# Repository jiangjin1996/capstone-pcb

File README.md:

# Analog Circuit Reliability for Low Earth Orbit Space Applications

In collaboration with the University of Saskatchewan, we are contributing a payload board
for the CubeSats Initiative in Canada for STEM (CUBICS). A CubeSat is a low cost, small
and approachable design for students “to engage in an end-to-end space mission
adapted to their needs and their level of comfort, expertise and readiness” (asc-csa.
gc.ca). Our payload studies the effects of space radiation on commonly used surface
mount analog Integrated Circuits (IC’s) in Low Earth Orbit (LEO). We compare different
shielding to see which provides a better effectiveness to weight ratio.

## Software

Available [here](https://github.com/kaitallaoua/capstone-cubeide)

## Setup

This project used KiCad `Version: 7.0.11-7.0.11~ubuntu22.04.1, release build` and a mix of windows builds.
Download KiCad [here](https://www.kicad.org/download/). KiCad 8 likely does work and I recommend you use it.

## Workflow

TBD (remove this once done): Someone needs to fork this repo to make further contributions to the project. Using an organization is best, I think UofS space team has one, maybe Regina team should make one? Regardless I will not be reviewing and accepting PR's to this repo.

Because using git for KiCad is like tracking binary files, I recommend to NOT rely on git handling merge conflicts. Avoid them entirely by letting only one person make changes on one branch at a time, make a PR, approve and merge and repeat and pass the baton to someone else to make changes.

## TODO

- Get I2C working (unlikely any KiCad changes)
- Get sinewave generation working 
- Add Voltage regulator
- Triple check we fit in PC104, on RADSAT-SK1 printout we dont fit in all holes, also supposed to be some notches?
- Optional: Use solder-attched external non volatile storage such as FLASH, EEPROM (or solder/glue micro sd down??)

The most substantial changes the sinwave generation. This task was assigned to Evan. Ultimately we could not get it working, thus I recommend to use a PWM wave gen from the mcu, likely add pre-amplification + current buffering, and pass it to a sharp drop off filter. The filter could be a dedicated one (probably better) or an op-amp driven one (butterworth?, wont have as good drop off without many stages).

UofRobotics is also making a PCB for their robot whose base is forked from this project, they may be a good reference for questions or idea sharing.

## Manufacturing

We used JLCPCB for `REV A` and `REV B` with great results. We also have nearly all parts ready for another revision. AT LEAST ONE MORE REVISION IS NEEDED SINCE THE FOLLOWING WERE FIXED AFTER `REV B`:

- IC1 footprint solder mask was incorrectly removed
- Micro SD card holder was facing the wrong way

Our manufacturing procedure was as follows:

Order from JLC (1 week delivery), Order from Mouser/Digikey (2-4 day delivery) -> Have all parts -> Go to ED435, use microscope, have one person assist finding parts, one pick+place, apply solder paste (min 4-5 hours)-> place in oven -> done

I recommend to use the parts list available from JLCPCB or PCBWay to assemble as much of the board for you as possible, it saves alot of time but honestly building it by hand it also not that bad. Either is fine.

JLC ordering tips:
1. Search for JLC production toolkit to generate the BOM, part placement file.
2. Generate the gerber files with time stamps in the folder name to avoid confusion (only gerber is a really bad name)
3. and do not forget to generate the drill file and put it into the gerber folder(you don't need the toolkit for this)
4. You can hand pick components on JLC if the system cannot find them automatically
5. Double check the 3d model pops up after the components are selected because sometimes the auto selected parts can be the wrong ones
6. Ask for boarding cleaning on the first page of ordering
7. Select add paste for unpopulated pad & step stencil opening for easier installation in case JLC doesn't have the components? (Not sure about this but we will see)
8. These might apply to other manufacturers as well

## Resources

[KiCad 6 STM32 PCB Design Full Tutorial - Phil's Lab #65](https://www.youtube.com/watch?v=aVUqaB0IMh4)

[PCB Design Final Touches (Tips & Checklist) - Phil's Lab #131](https://www.youtube.com/watch?v=g4m91gv-4oQ)

## Front PCB

## Back PCB

## Front Copper Layer

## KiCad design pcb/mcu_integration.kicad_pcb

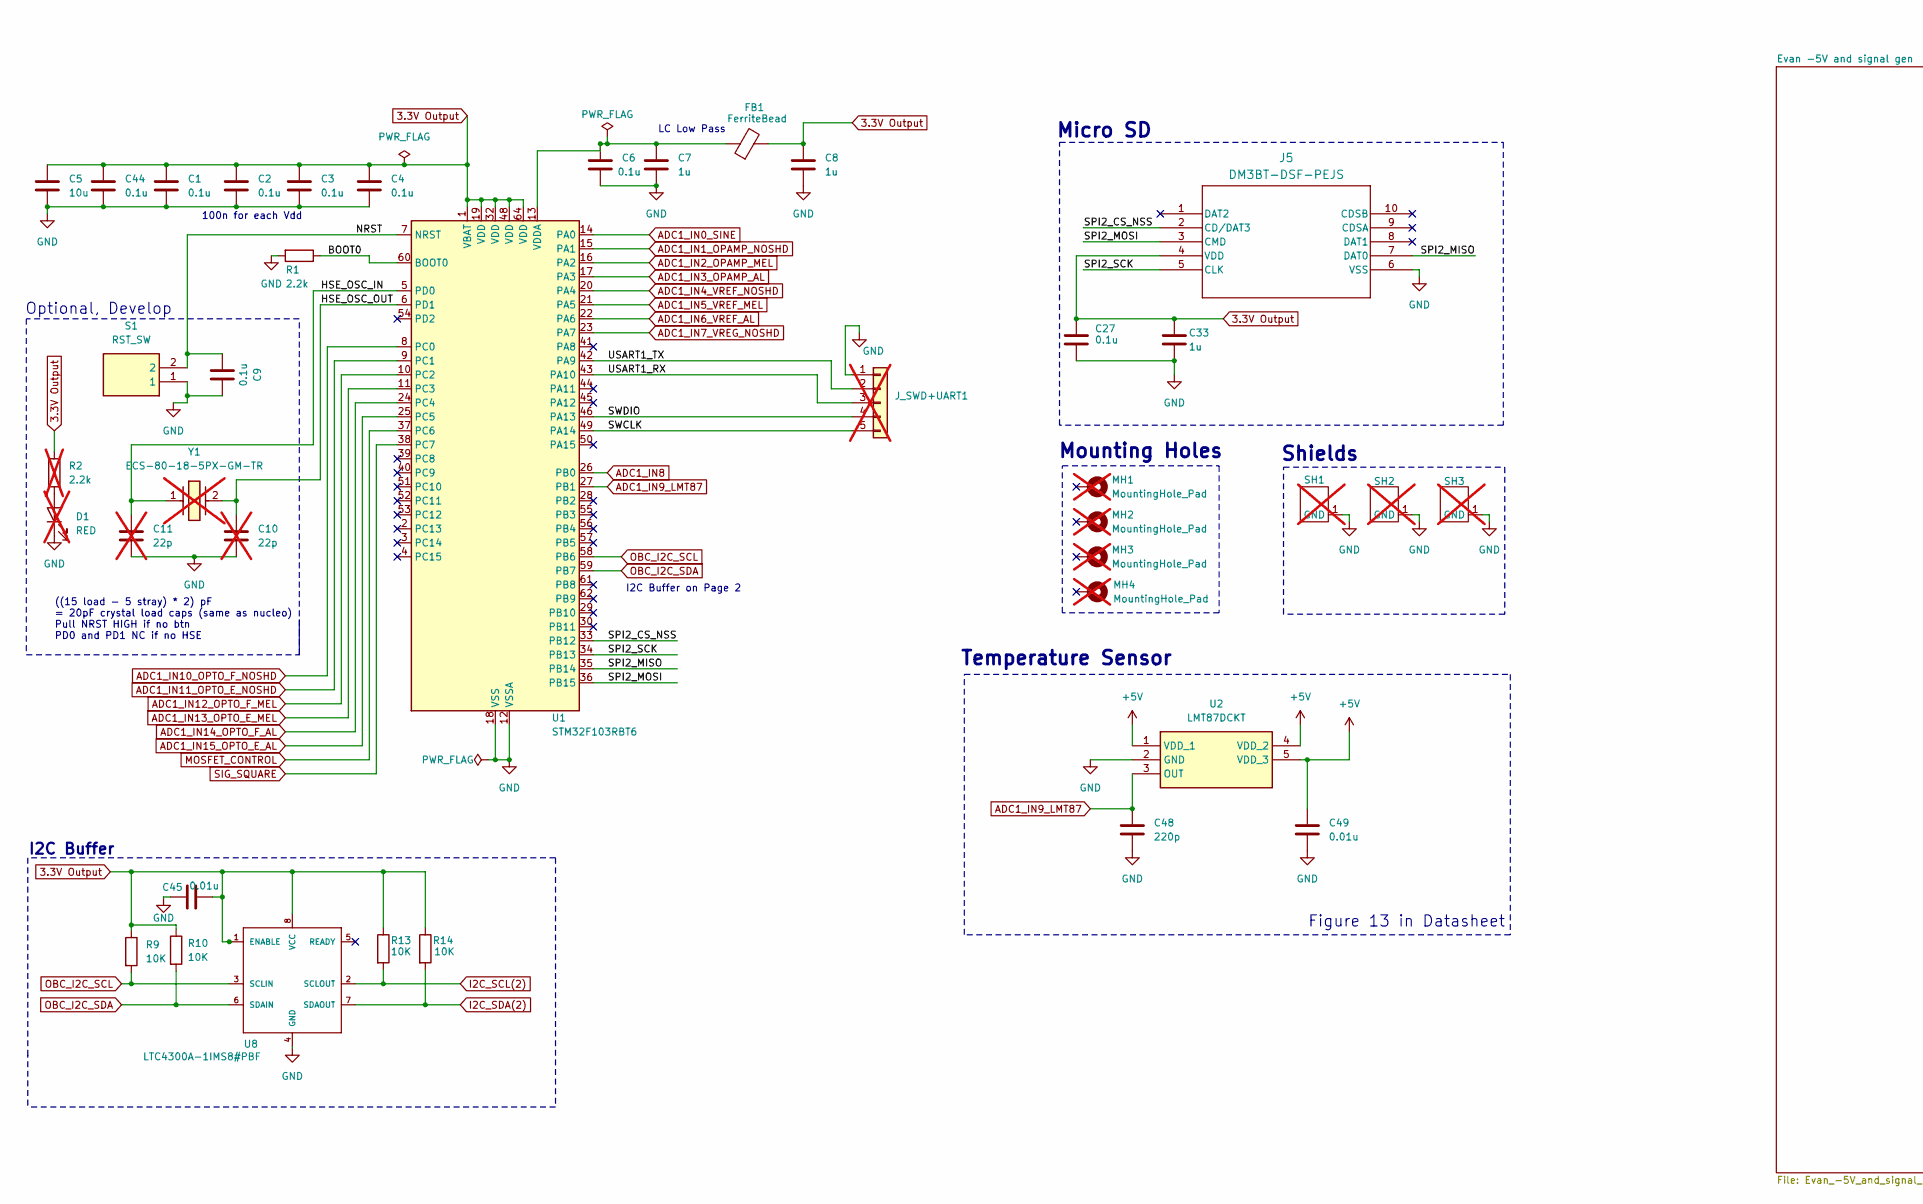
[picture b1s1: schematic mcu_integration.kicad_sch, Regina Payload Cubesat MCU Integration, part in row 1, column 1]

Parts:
C1, C2, C3, C4, C6, C9, C27, C44: 0.1u; C_0402_1005Metric; MPN C0402C104J4RALTU
C5: 10u; C_0603_1608Metric; MPN C0603C106M9PACTU
C7, C8, C33: 1u; C_0402_1005Metric; MPN 0402ZD105KAT2A
C10, C11: 22p; C_0402_1005Metric; not fitted
C45, C49: 0.01u; C_0402_1005Metric; MPN C0402C103J4RALTU
C48: 220p; C_0402_1005Metric; MPN C0402C221K8RACTU
D1: RED; LED_0603_1608Metric; not fitted
FB1: FerriteBead; L_0603_1608Metric; MPN GZ1608E601TF
J5: DM3BT-DSF-PEJS; DM3BT_DSF_PEJS; MPN DM3BT-DSF-PEJS
J_SWD+UART1: J_SWD+UART1; PinHeader_1x05_P2.54mm_Vertical; not fitted
MH1, MH2, MH3, MH4: MountingHole_Pad; MountingHole_3.18mm_6.35mm_Pad; not fitted
R1: 2.2k; R_0402_1005Metric; MPN CRCW04022K20FKTD
R2: 2.2k; R_0402_1005Metric; MPN CRCW04022K20FKTD; not fitted
R9, R10, R13, R14: 10K; R_0402_1005Metric; MPN CRCW040210K0FKTD
S1: RST_SW; 95C04A3GWRT; Mouser Part Number 706-95C04A3GWRT
SH1: AD844 Shield; not fitted
SH2: FOD814 Shield; not fitted
SH3: REF192 Shield; not fitted
U1: STM32F103RBT6; LQFP-64_10x10mm_P0.5mm; MPN STM32F103RBT6
U2: LMT87DCKT; SOT65P210X110-5N; Mouser Part Number 595-LMT87DCKT
U8: LTC4300A-1IMS8#PBF; LTC4300A-1IMS8_PBF; MPN LTC4300A-1IMS8#PBF
Y1: ECS-80-18-5PX-GM-TR; ECS80185PXGMTR; Mouser Part Number 520-80-18-5PX-GM-TR; not fitted

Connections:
3.3V Output: C1.1, C2.1, C3.1, C4.1, C5.1, C8.1, C27.1, C33.1, C44.1, C45.2, FB1.2, J5.4 (VDD), R2.1, R9.1, R10.1, R13.1, R14.1, U1.1 (VBAT), U1.19 (VDD), U1.32 (VDD), U1.48 (VDD), U1.64 (VDD), U8.1 (ENABLE), U8.8 (VCC); also elsewhere on the board
+5V: C49.1, U2.1 (VDD_1), U2.4 (VDD_2), U2.5 (VDD_3); also elsewhere on the board
/BOOT0: R1.1, U1.60 (BOOT0)
/HSE_OSC_IN: C11.1, U1.5 (PD0), Y1.1
/HSE_OSC_OUT: C10.1, U1.6 (PD1), Y1.2
/NRST: C9.2, S1.2, U1.7 (NRST)
/SPI2_CS_NSS: J5.2 (CD/DAT3), U1.33 (PB12)
/SPI2_MISO: J5.7 (DAT0), U1.35 (PB14)
/SPI2_MOSI: J5.3 (CMD), U1.36 (PB15)
/SPI2_SCK: J5.5 (CLK), U1.34 (PB13)
/SWCLK: J_SWD+UART1.5, U1.49 (PA14)
/SWDIO: J_SWD+UART1.4, U1.46 (PA13)
/USART1_RX: J_SWD+UART1.3, U1.43 (PA10)
/USART1_TX: J_SWD+UART1.2, U1.42 (PA9)
ADC1_IN0_SINE: U1.14 (PA0); also elsewhere on the board
ADC1_IN1_OPAMP_NOSHD: U1.15 (PA1); also elsewhere on the board
ADC1_IN2_OPAMP_MEL: U1.16 (PA2); also elsewhere on the board
ADC1_IN3_OPAMP_AL: U1.17 (PA3); also elsewhere on the board
ADC1_IN4_VREF_NOSHD: U1.20 (PA4); also elsewhere on the board
ADC1_IN5_VREF_MEL: U1.21 (PA5); also elsewhere on the board
ADC1_IN6_VREF_AL: U1.22 (PA6); also elsewhere on the board
ADC1_IN7_VREG_NOSHD: U1.23 (PA7)
ADC1_IN8: U1.26 (PB0)
ADC1_IN9_LMT87: C48.1, U1.27 (PB1), U2.3 (OUT); also elsewhere on the board
ADC1_IN10_OPTO_F_NOSHD: U1.8 (PC0); also elsewhere on the board
ADC1_IN11_OPTO_E_NOSHD: U1.9 (PC1); also elsewhere on the board
ADC1_IN12_OPTO_F_MEL: U1.10 (PC2); also elsewhere on the board
ADC1_IN13_OPTO_E_MEL: U1.11 (PC3); also elsewhere on the board
ADC1_IN14_OPTO_F_AL: U1.24 (PC4); also elsewhere on the board
ADC1_IN15_OPTO_E_AL: U1.25 (PC5); also elsewhere on the board
GND: C1.2, C2.2, C3.2, C4.2, C5.2, C6.2, C7.2, C8.2, C9.1, C10.2, C11.2, C27.2, C33.2, C44.2, C45.1, C48.2, C49.2, D1.1 (K), J5.6 (VSS), J_SWD+UART1.1, R1.2, S1.1, SH1.1 (GND_1), SH2.1 (GND_1), SH3.1 (GND_1), U1.12 (VSSA), U1.18 (VSS), U1.31 (VSS), U1.47 (VSS), U1.63 (VSS), U2.2 (GND), U8.4 (GND); also elsewhere on the board
I2C_SCL(2): R13.2, U8.2 (SCLOUT); also elsewhere on the board
I2C_SDA(2): R14.2, U8.7 (SDAOUT); also elsewhere on the board
MOSFET_CONTROL: U1.37 (PC6); also elsewhere on the board
unnamed: C6.1, C7.1, FB1.1, U1.13 (VDDA)
OBC_I2C_SCL: R9.2, U1.58 (PB6), U8.3 (SCLIN)
OBC_I2C_SDA: R10.2, U1.59 (PB7), U8.6 (SDAIN)
SIG_SQUARE: U1.38 (PC7); also elsewhere on the board

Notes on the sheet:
((15 load - 5 stray) * 2) pF = 20pF crystal load caps (same as nucleo) Pull NRST HIGH if no btn PD0 and PD1 NC if no HSE
Mounting Holes
Micro SD
Optional, Develop
Shields
I2C Buffer on Page 2
Temperature Sensor
100n for each Vdd
Figure 13 in Datasheet
LC Low Pass
I2C Buffer

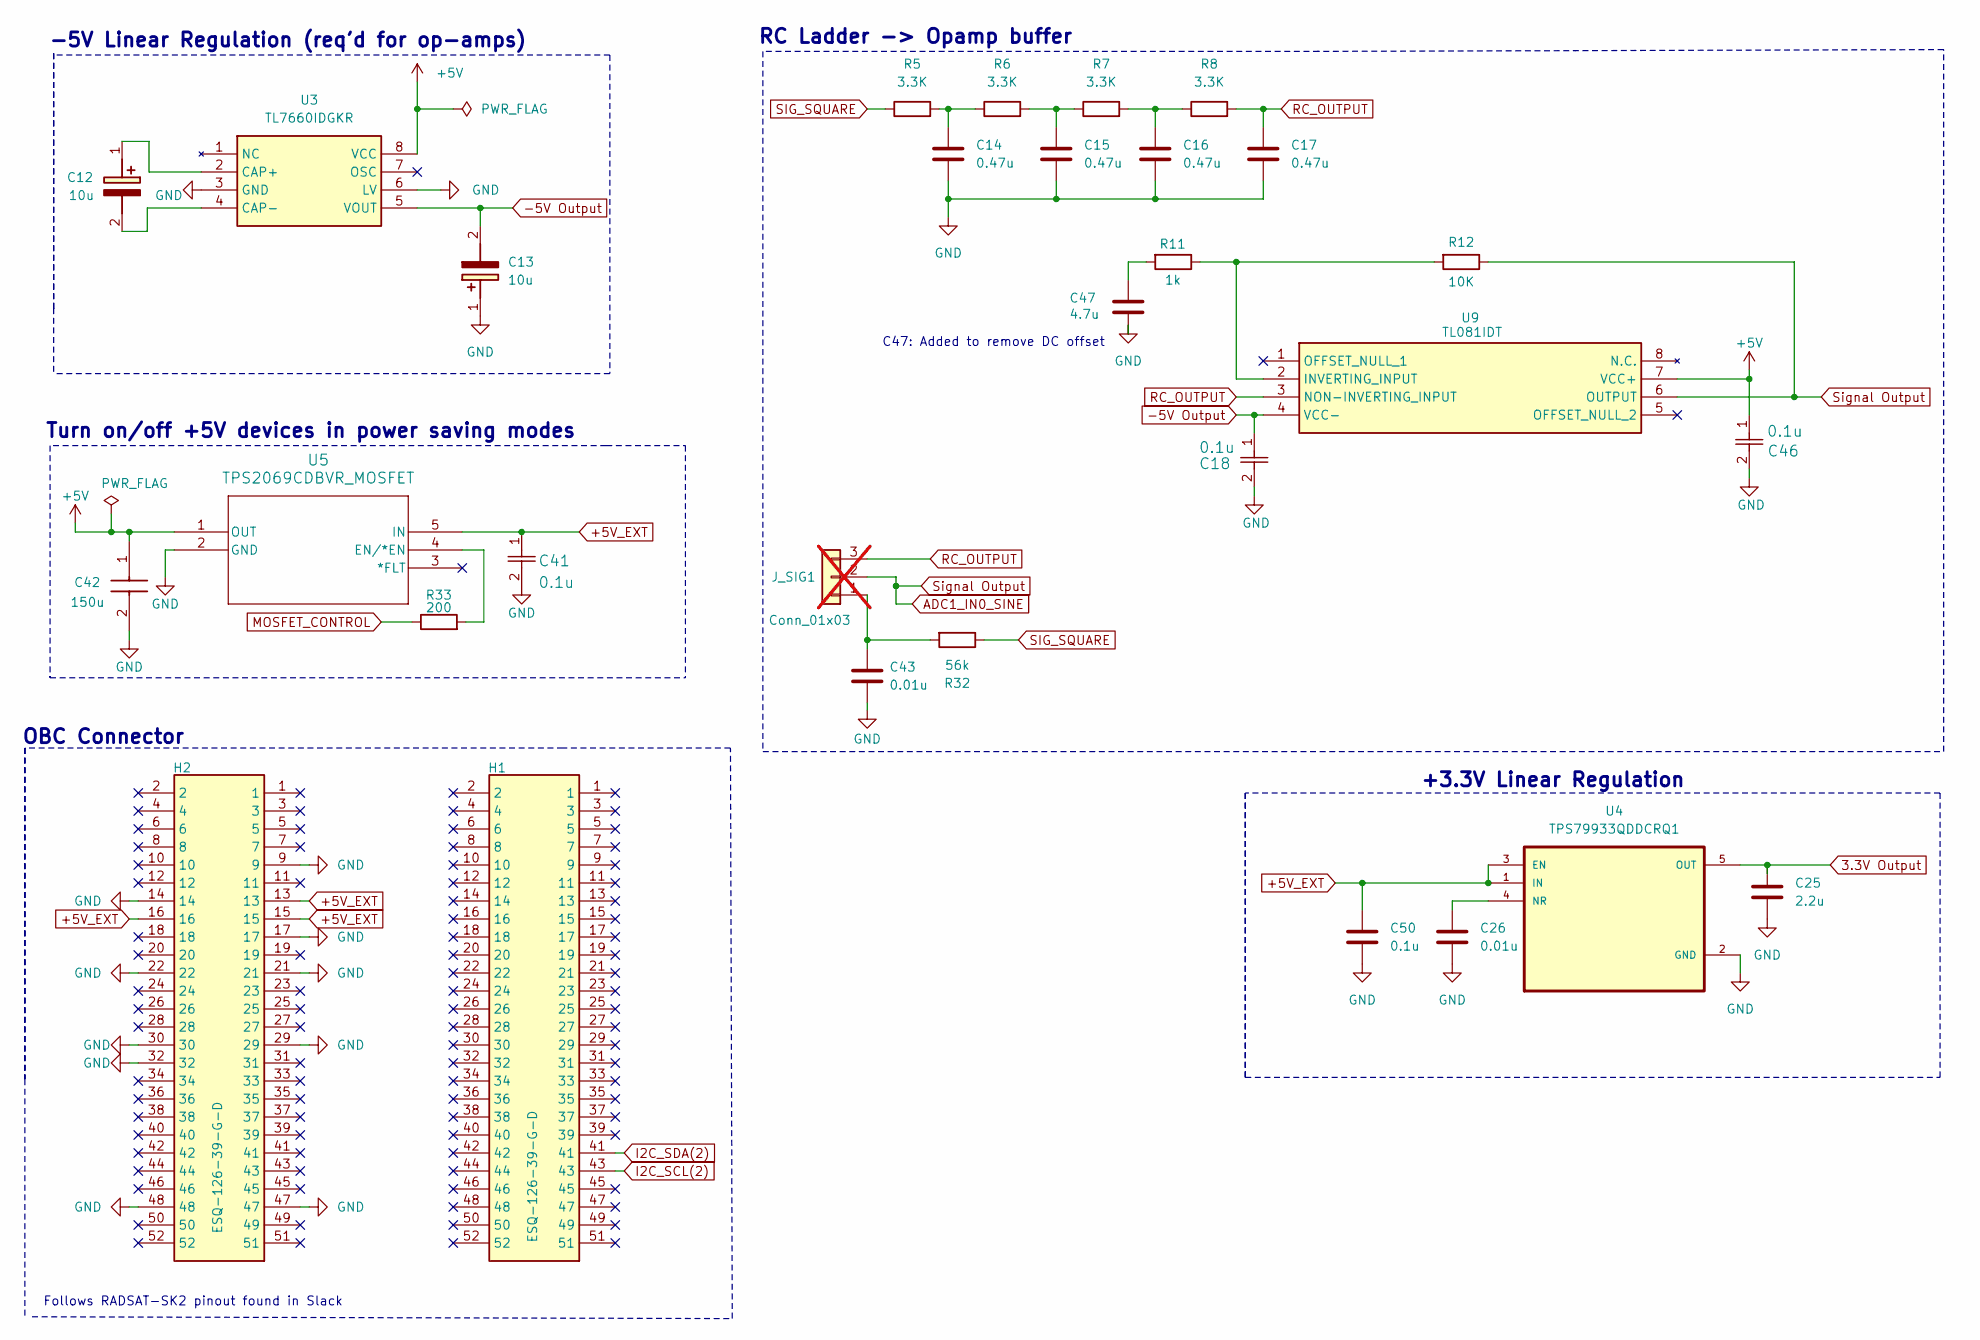
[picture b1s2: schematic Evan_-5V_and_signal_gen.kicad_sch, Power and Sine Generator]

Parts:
C12, C13: 10u; C_0805_2012Metric; Mouser Part Number 80-T495D106K035
C14, C15, C16, C17: 0.47u; C_0402_1005Metric; MPN KGM05AR51A474KH
C18, C41, C46: 0.1u; C_0805_2012Metric; MPN C0805C104J4RALTU
C25: 2.2u; C_0603_1608Metric; MPN C0603C225K8RACTU
C26, C43: 0.01u; C_0402_1005Metric; MPN C0402C103J4RALTU
C42: 150u; CAPC3225X280N_150U; Mouser Part Number 187-CL32A157MQVNNNE
C47: 4.7u; C_0805_2012Metric; MPN C0805C475J4RACTU
C50: 0.1u; C_0402_1005Metric; MPN C0402C104J4RALTU
H1, H2: ESQ-126-39-G-D; RHDR52W64P254_2X26_6654X495X1135P; Mouser Part Number 200-ESQ12639LD
J_SIG1: Conn_01x03; PinHeader_1x03_P2.54mm_Vertical; not fitted
R5, R6, R7, R8: 3.3K; R_0402_1005Metric; MPN CRCW04023K30FKTD
R11: 1k; R_0402_1005Metric; MPN CRCW04021K00FKTD
R12: 10K; R_0402_1005Metric; MPN CRCW040210K0FKTD
R32: 56k; R_0402_1005Metric; MPN CRCW040256K0FKTD
R33: 200; R_0402_1005Metric; MPN CRCW0402200RFKTD
U3: TL7660IDGKR; SOP65P490X110-8N-actual; Mouser Part Number 595-TL7660IDGKR
U4: TPS79933QDDCRQ1; SOT95P280X110-5N; MPN TPS79933QDDCRQ1
U5: TPS2069CDBVR_MOSFET; DBV5_TEX_MF; MPN TPS2069CDBVR
U9: TL081IDT; SOIC127P600X175-8N; Mouser Part Number 511-TL081IDT

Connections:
3.3V Output: C25.1, U4.5 (OUT); also elsewhere on the board
+5V: C42.1, C46.1, U3.8 (VCC), U5.1 (OUT), U9.7 (VCC+); also elsewhere on the board
+5V_EXT: C41.1, C50.1, H2.13, H2.15, H2.16, U4.1 (IN), U4.3 (EN), U5.5 (IN)
-5V Output: C13.2 (-), C18.1, U3.5 (VOUT), U9.4 (VCC-); also elsewhere on the board
ADC1_IN0_SINE: J_SIG1.2, R12.1, U9.6 (OUTPUT); also elsewhere on the board
GND: C13.1 (+), C14.2, C15.2, C16.2, C17.2, C18.2, C25.2, C26.2, C41.2, C42.2, C43.1, C46.2, C47.2, C50.2, H2.9, H2.14, H2.17, H2.21, H2.22, H2.29, H2.30, H2.32, H2.47, H2.48, U3.3 (GND), U3.6 (LV), U4.2 (GND), U5.2 (GND); also elsewhere on the board
I2C_SCL(2): H1.43; also elsewhere on the board
I2C_SDA(2): H1.41; also elsewhere on the board
MOSFET_CONTROL: R33.1; also elsewhere on the board
unnamed: C12.1 (+), U3.2 (CAP+)
unnamed: C12.2 (-), U3.4 (CAP-)
unnamed: C14.1, R5.2, R6.1
unnamed: C15.1, R6.2, R7.1
unnamed: C16.1, R7.2, R8.1
unnamed: C47.1, R11.2
unnamed: C43.2, J_SIG1.1, R32.2
unnamed: C26.1, U4.4 (NR)
unnamed: R33.2, U5.4 (EN/*EN)
unnamed: R11.1, R12.2, U9.2 (INVERTING_INPUT)
RC_OUTPUT: C17.1, J_SIG1.3, R8.2, U9.3 (NON-INVERTING_INPUT)
SIG_SQUARE: R5.1, R32.1; also elsewhere on the board

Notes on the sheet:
OBC Connector
+3.3V Linear Regulation
-5V Linear Regulation (req'd for op-amps)
RC Ladder -> Opamp buffer
Turn on/off +5V devices in power saving modes
Follows RADSAT-SK2 pinout found in Slack
C47: Added to remove DC offset

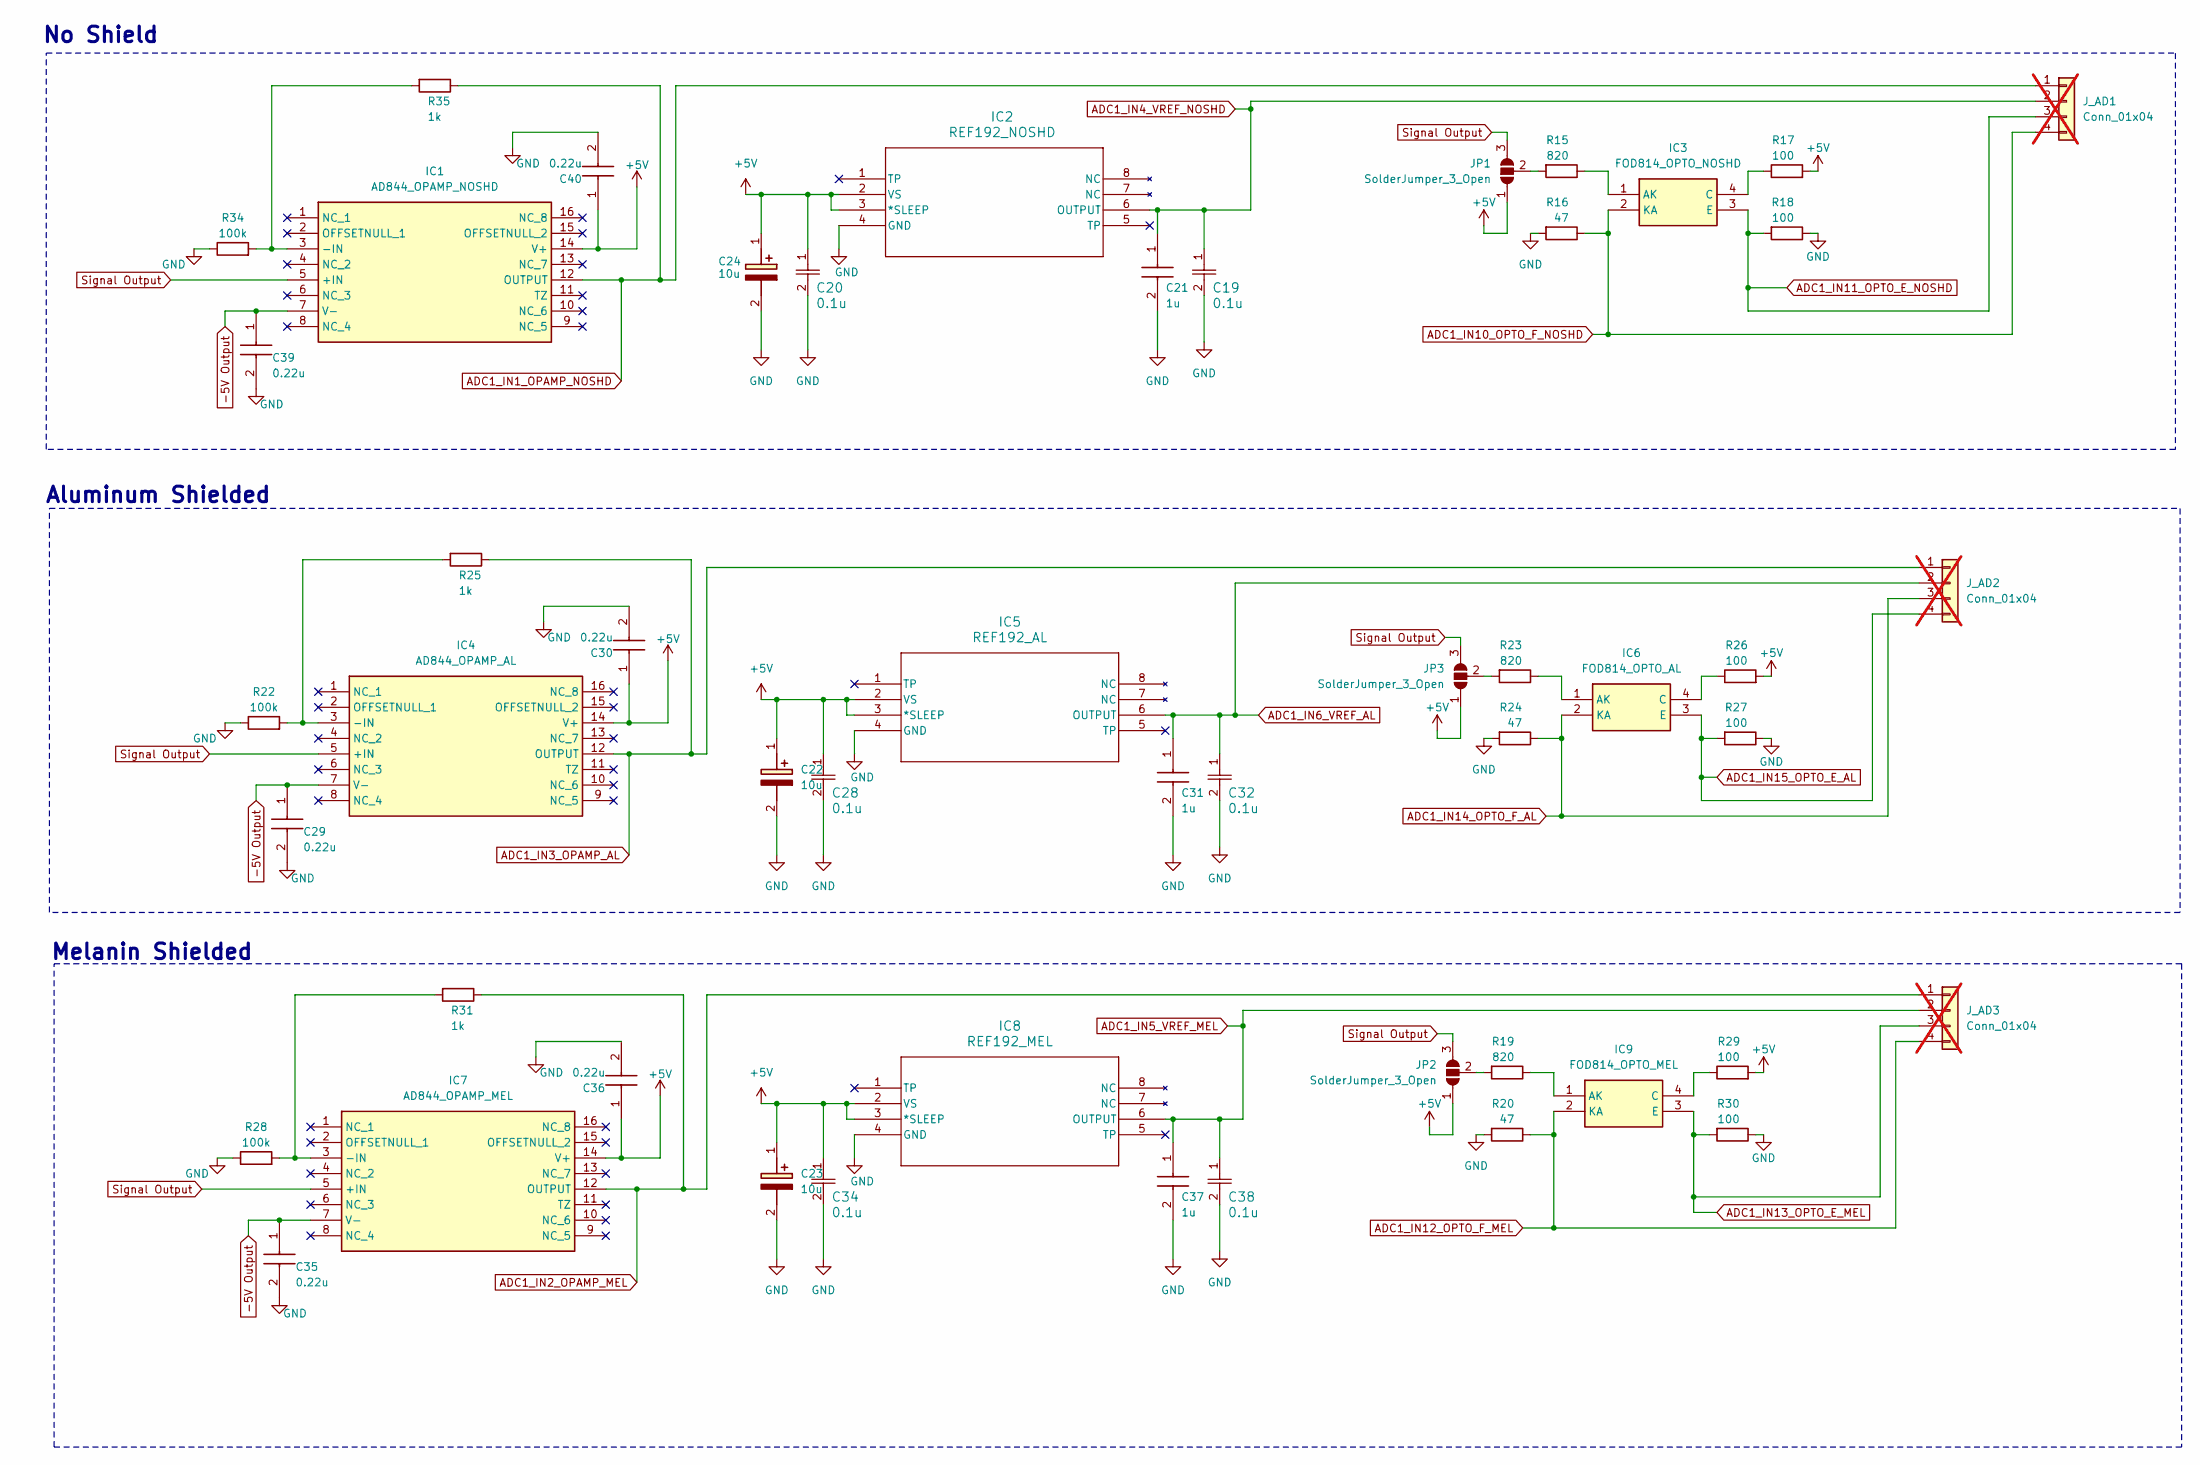
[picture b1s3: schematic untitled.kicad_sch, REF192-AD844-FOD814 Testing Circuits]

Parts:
C19, C20, C28, C32, C34, C38: 0.1u; C_0805_2012Metric; MPN C0805C104J4RALTU
C21, C31, C37: 1u; C0805-1u; Mouser Part Number 80-C0805C105Z5VACTU
C22, C23, C24: 10u; C_0805_2012Metric; Mouser Part Number 80-T495D106K035
C29, C30, C35, C36, C39, C40: 0.22u; C0805-0.22u; MPN C0805C224J4RALTU
IC1: AD844_OPAMP_NOSHD; SOIC127P1032X265-16N-AD844; Mouser Part Number 584-AD844JRZ-16-R7
IC2: REF192_NOSHD; R_8_ADI-REF; MPN REF192GSZ
IC3: FOD814_OPTO_NOSHD; SOP254P1016X385-4N-FOD; Mouser Part Number 512-FOD814SD
IC4: AD844_OPAMP_AL; SOIC127P1032X265-16N-AD844; Mouser Part Number 584-AD844JRZ-16-R7
IC5: REF192_AL; R_8_ADI-REF; MPN REF192GSZ
IC6: FOD814_OPTO_AL; SOP254P1016X385-4N-FOD; Mouser Part Number 512-FOD814SD
IC7: AD844_OPAMP_MEL; SOIC127P1032X265-16N-AD844; Mouser Part Number 584-AD844JRZ-16-R7
IC8: REF192_MEL; R_8_ADI-REF; MPN REF192GSZ
IC9: FOD814_OPTO_MEL; SOP254P1016X385-4N-FOD; Mouser Part Number 512-FOD814SD
JP1, JP2, JP3: SolderJumper_3_Open; SolderJumper-3_P2.0mm_Open_TrianglePad1.0x1.5mm
J_AD1, J_AD2, J_AD3: Conn_01x04; PinHeader_1x04_P2.54mm_Vertical; not fitted
R15, R19, R23: 820; R_0402_1005Metric; MPN CRCW0402820RFKED
R16, R20, R24: 47; R_0402_1005Metric; MPN CRCW040247R0FKTD
R17, R18, R26, R27, R29, R30: 100; R_0402_1005Metric; MPN CRCW0402100RFKTD
R22, R28, R34: 100k; R_0402_1005Metric; MPN CRCW0402100KFKTD
R25, R31, R35: 1k; R_0402_1005Metric; MPN CRCW04021K00FKTD

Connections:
+5V: C20.1, C22.1 (+), C23.1 (+), C24.1 (+), C28.1, C30.1, C34.1, C36.1, C40.1, IC1.14 (V+), IC2.2 (VS), IC2.3 (*SLEEP), IC4.14 (V+), IC5.2 (VS), IC5.3 (*SLEEP), IC7.14 (V+), IC8.2 (VS), IC8.3 (*SLEEP), JP1.1 (A), JP2.1 (A), JP3.1 (A), R17.2, R26.2, R29.2; also elsewhere on the board
-5V Output: C29.1, C35.1, C39.1, IC1.7 (V-), IC4.7 (V-), IC7.7 (V-); also elsewhere on the board
ADC1_IN0_SINE: IC1.5 (+IN), IC4.5 (+IN), IC7.5 (+IN), JP1.3 (B), JP2.3 (B), JP3.3 (B); also elsewhere on the board
ADC1_IN1_OPAMP_NOSHD: IC1.12 (OUTPUT), J_AD1.1, R35.1; also elsewhere on the board
ADC1_IN2_OPAMP_MEL: IC7.12 (OUTPUT), J_AD3.1, R31.1; also elsewhere on the board
ADC1_IN3_OPAMP_AL: IC4.12 (OUTPUT), J_AD2.1, R25.1; also elsewhere on the board
ADC1_IN4_VREF_NOSHD: C19.1, C21.1, IC2.6 (OUTPUT), J_AD1.2; also elsewhere on the board
ADC1_IN5_VREF_MEL: C37.1, C38.1, IC8.6 (OUTPUT), J_AD3.2; also elsewhere on the board
ADC1_IN6_VREF_AL: C31.1, C32.1, IC5.6 (OUTPUT), J_AD2.2; also elsewhere on the board
ADC1_IN10_OPTO_F_NOSHD: IC3.2 (KA), J_AD1.4, R16.1; also elsewhere on the board
ADC1_IN11_OPTO_E_NOSHD: IC3.3 (E), J_AD1.3, R18.2; also elsewhere on the board
ADC1_IN12_OPTO_F_MEL: IC9.2 (KA), J_AD3.4, R20.1; also elsewhere on the board
ADC1_IN13_OPTO_E_MEL: IC9.3 (E), J_AD3.3, R30.2; also elsewhere on the board
ADC1_IN14_OPTO_F_AL: IC6.2 (KA), J_AD2.3, R24.1; also elsewhere on the board
ADC1_IN15_OPTO_E_AL: IC6.3 (E), J_AD2.4, R27.2; also elsewhere on the board
GND: C19.2, C20.2, C21.2, C22.2 (-), C23.2 (-), C24.2 (-), C28.2, C29.2, C30.2, C31.2, C32.2, C34.2, C35.2, C36.2, C37.2, C38.2, C39.2, C40.2, IC2.4 (GND), IC5.4 (GND), IC8.4 (GND), R16.2, R18.1, R20.2, R22.1, R24.2, R27.1, R28.1, R30.1, R34.1; also elsewhere on the board
unnamed: IC1.3 (-IN), R34.2, R35.2
unnamed: IC3.1 (AK), R15.1
unnamed: IC3.4 (C), R17.1
unnamed: IC4.3 (-IN), R22.2, R25.2
unnamed: IC6.1 (AK), R23.1
unnamed: IC6.4 (C), R26.1
unnamed: IC7.3 (-IN), R28.2, R31.2
unnamed: IC9.1 (AK), R19.1
unnamed: IC9.4 (C), R29.1
unnamed: JP1.2 (C), R15.2
unnamed: JP2.2 (C), R19.2
unnamed: JP3.2 (C), R23.2

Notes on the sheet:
Aluminum Shielded
Melanin Shielded
No Shield

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
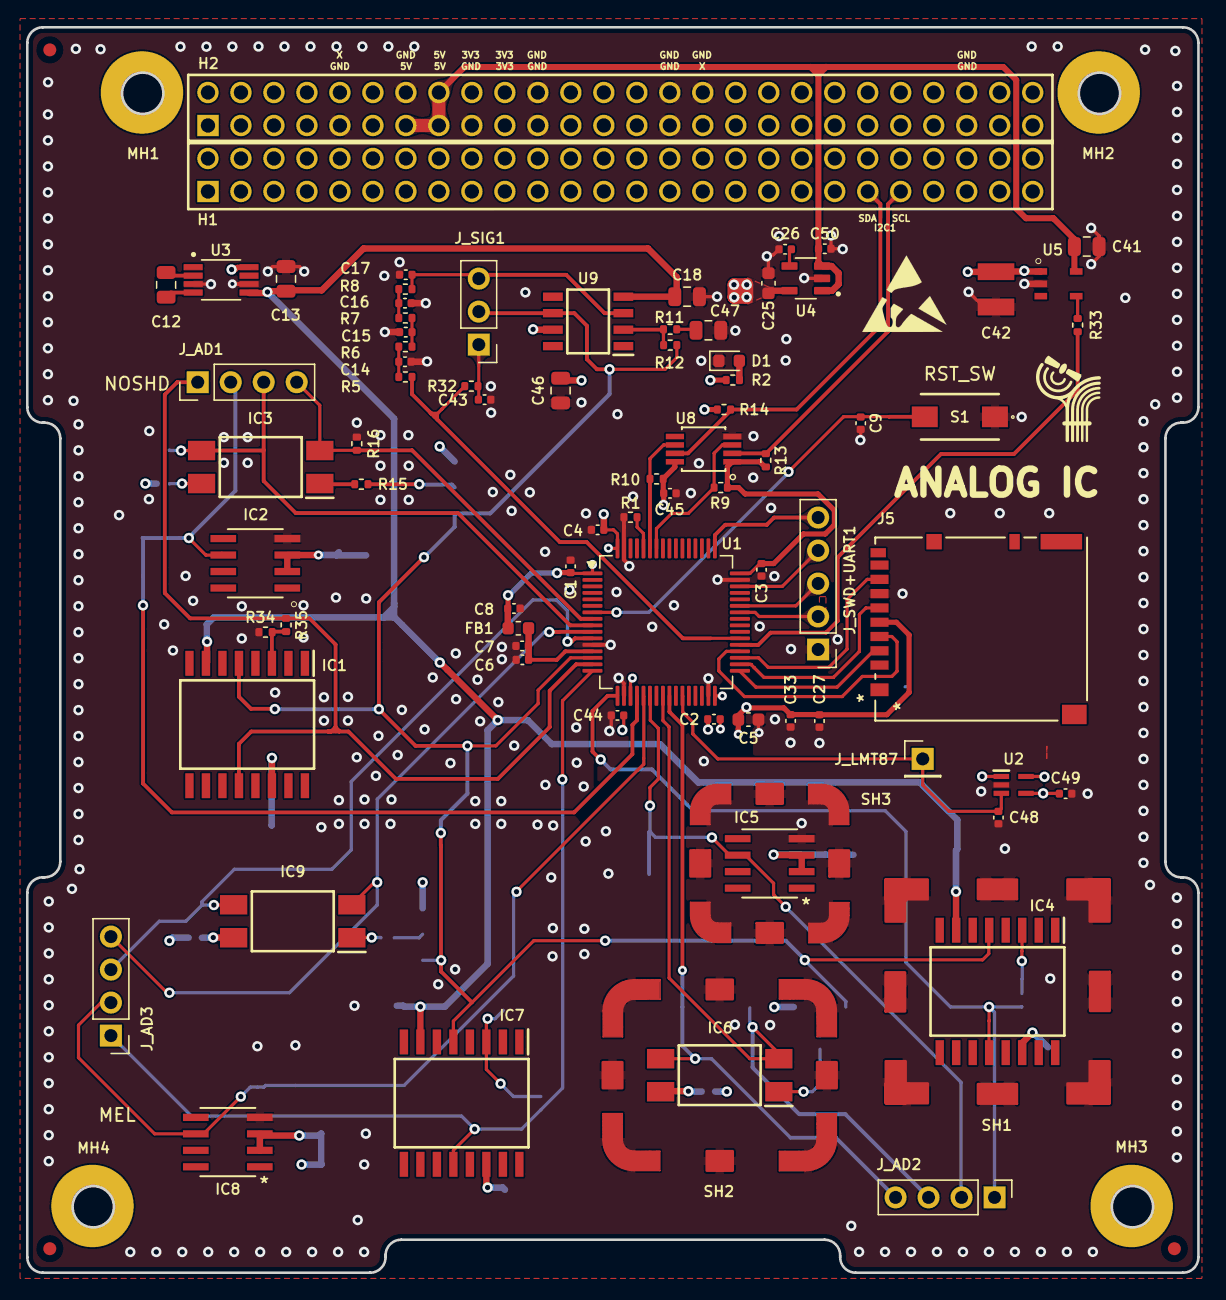
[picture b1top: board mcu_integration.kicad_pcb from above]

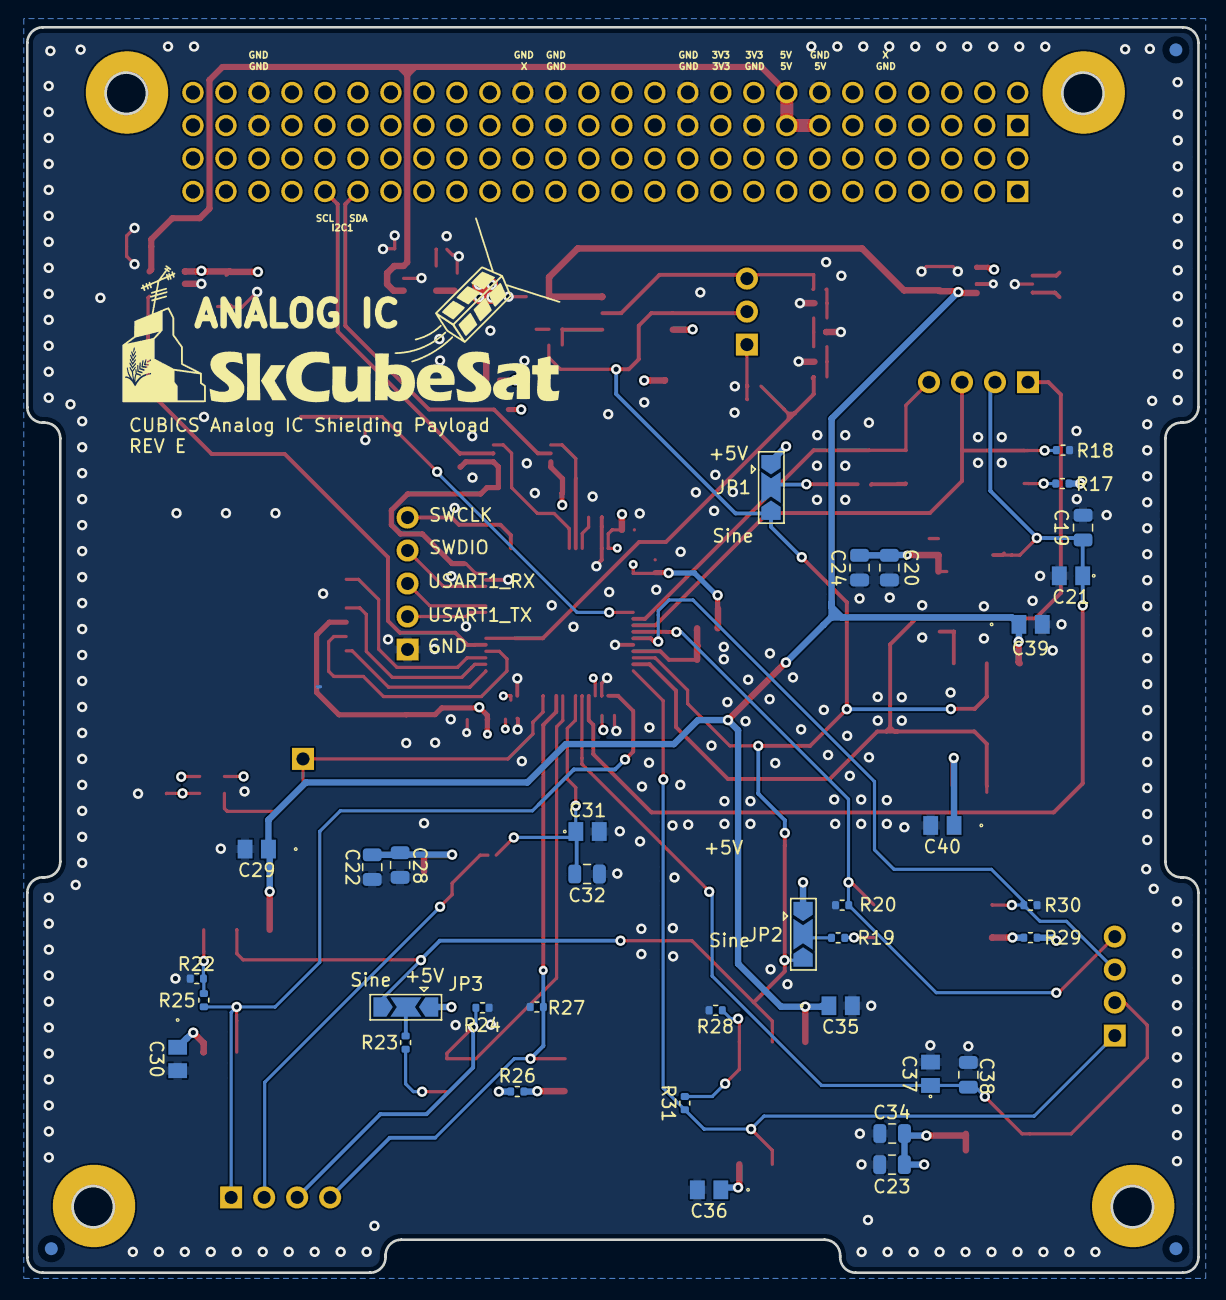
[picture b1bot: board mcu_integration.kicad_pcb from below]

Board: 4 copper layers, 90.2 x 95.9 mm, 118 parts (35 on the bottom side), 59 nets.

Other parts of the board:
J_LMT87: Conn_01x01; PinHeader_1x01_P2.54mm_Vertical

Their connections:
ADC1_IN9_LMT87: J_LMT87.1; also elsewhere on the board

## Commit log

2024-11-17 Create RAD2-GEN-ICD-001A-Subsystem_External_Connections.xlsx
    CSKB Pin out file
2024-11-24 Working Commit - Nov24
2024-12-01 FIxed PCB shape and mounting holes
2024-12-08 SD card change
2025-01-26 Routed all connections
2025-02-11 Added LM35 Temp Sensor
2025-02-23 Added GND and PWR planes
2025-02-23 Connected GND connections to GND plane
2025-03-02 Added +5v connections
2025-03-09 Added RC Ladder Circuit
2025-03-09 Routed all RC ladder connections
2025-03-16 Fixed PCB silkscreen
2025-03-26 Added silkscreen and changed diode footprints
2025-04-03 readme update
2025-05-11 Added reset button & LED, fixed SD card overhang
2025-05-11 Added non-inverting amplifier to RC Ladder and Changed header pin
2025-05-18 Fixed silkscreen and component values
2025-06-09 Updated CSKB connector
2025-06-22 Added missing decoupling capacitor + changed capacitors footprint
2025-08-10 Added copper pours to top and bottom layer, added 3.3v plane, spaced ICs to fit melanin caps, ungrounded connection pads, added stitching vias to outer edge
2025-08-17 Conformed to JLC DFM
2025-08-24 Added Shield Footprints
2025-08-31 Adjusted spacing of shields to allow for easier soldering
2025-09-07 Fixed Shield Solder Mask
2025-09-07 Moved resistors and capacitors to back of board
2025-09-21 Moved control IC capacitors to back of board to conform with other IC groups
2025-12-14 Added switchable inputs for opamps
2026-01-04 Moved Shielded ICs
2026-01-11 Changed IC orientation
2026-01-11 Production files
2026-01-16 Thermal Reliefs and Blind Vias
    - Added back thermal reliefs to shields
    - Swapped power vias to not be drilled across all layers
2026-02-02 Replaced LM35 temperature sensor with LMT87
2026-02-02 Changed C18, C19, C20, C28, C32, C34, C38, C41, C46, C47 footprints to 0805
2026-02-08 Replaced blind vias with through vias to comply with jlcpcb
2026-02-15 fixed 3D model file paths and added CSKB pin labels
2026-02-15 Started selecting BOM
2026-02-15 Added more to the BOM
2026-02-16 Finished BOM and fixed file paths for 3D models
2026-02-16 Updated BOM
2026-02-18 renewing files for manufacturing quote
2026-02-22 added 3D models for melanin domes
2026-02-27 Fixed the SD card STEP file
2026-03-01 Moved SD card to top of board
2026-03-06 updated component labels
2026-03-08 Added 3.3V regulator
2026-03-09 updated schematic lables
2026-03-15 Changed spacing of test ICs to allow for larger melanin domes
2026-03-16 Updated 3D Models
    Added model for 3V3 Linear voltage regulator and rescaled models for melanin shields
2026-03-23 Made some minor routing adjustments
2026-05-02 Made minor changes for routing and decoup caps
2026-05-06 Adjusted some things
2026-05-09 Fixed i2c teardrops
2026-05-09 Finished C25 BOM designation
2026-05-12 Added Fiducials
2026-05-30 Started fixing the BOM
2026-05-31 Did more work on the BOM
2026-05-31 changed STM32 part back to original
2026-05-31 Added ferrite bead
